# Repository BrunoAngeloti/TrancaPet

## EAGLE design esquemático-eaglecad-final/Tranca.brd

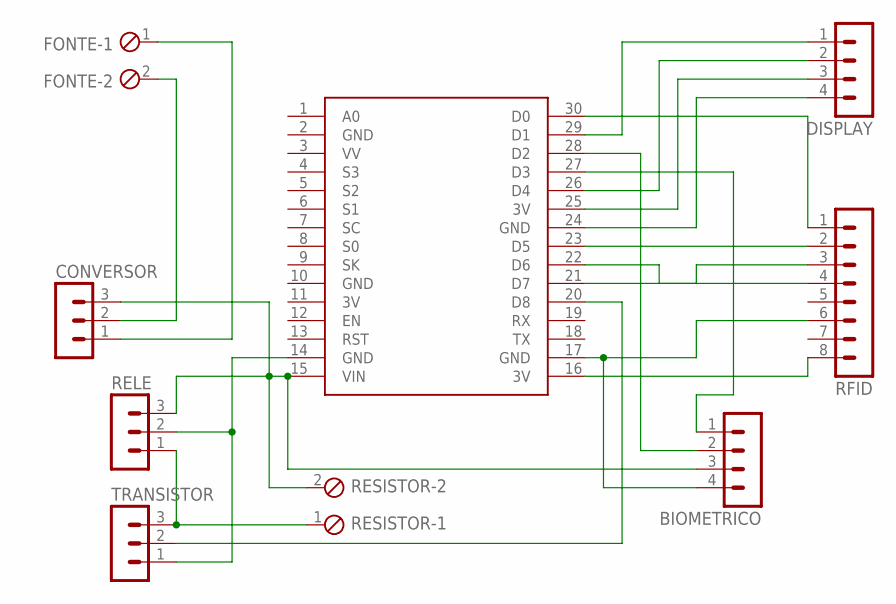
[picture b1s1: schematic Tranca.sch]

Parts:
BIOMETRICO: MA04-1
CONVERSOR: MA03-1
DISPLAY: MA04-1
FONTE: MPT2; 2POL254
RELE: MA03-1
RESISTOR: MPT2; 2POL254
RFID: MA08-1
TRANSISTOR: MA03-1
U$1: NODEMCU

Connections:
3V: U$1.11 (3V)
GND: U$1.2 (GND), U$1.10 (GND)
unnamed: DISPLAY.4, U$1.24 (GND)
unnamed: DISPLAY.3, U$1.25 (3V)
unnamed: DISPLAY.2, U$1.26 (D4)
unnamed: DISPLAY.1, U$1.29 (D1)
unnamed: TRANSISTOR.2, U$1.20 (D8)
unnamed: RFID.2, U$1.23 (D5)
unnamed: RFID.3, U$1.21 (D7)
unnamed: RFID.4, U$1.22 (D6)
unnamed: BIOMETRICO.4, RFID.6, U$1.17 (GND)
unnamed: RELE.2, TRANSISTOR.1, U$1.14 (GND)
unnamed: RFID.8, U$1.16 (3V)
unnamed: BIOMETRICO.2, U$1.28 (D2)
unnamed: BIOMETRICO.1, U$1.27 (D3)
unnamed: RELE.1, RESISTOR.1, TRANSISTOR.3
unnamed: CONVERSOR.2, FONTE.2
unnamed: RFID.1, U$1.30 (D0)
unnamed: CONVERSOR.1, FONTE.1
unnamed: BIOMETRICO.3, CONVERSOR.3, RELE.3, RESISTOR.2, U$1.15 (VIN)

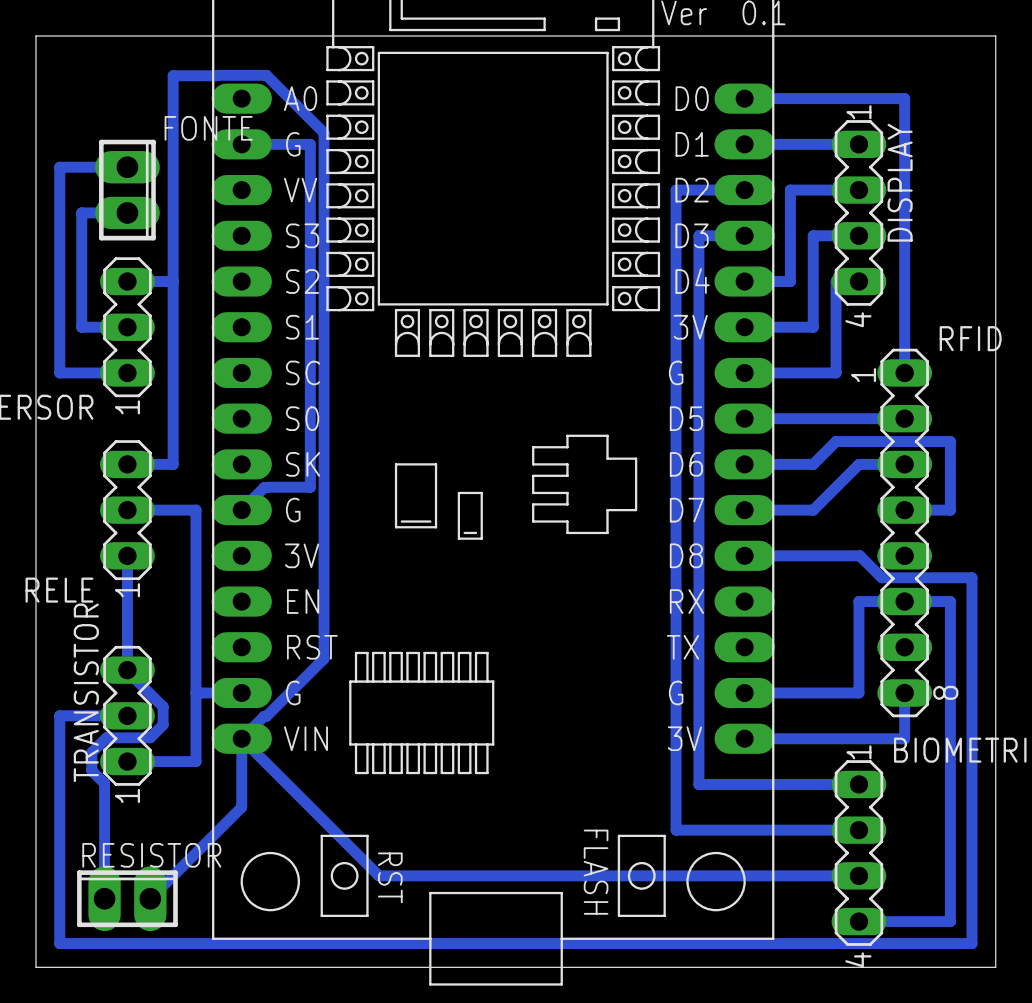
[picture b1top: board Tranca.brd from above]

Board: 2 copper layers, 53.3 x 51.7 mm, 9 parts (0 on the bottom side), 19 nets.

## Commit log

2021-07-05 Projeto finalizado
